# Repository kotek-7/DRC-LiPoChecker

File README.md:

リポチェッカーです  
KiCad ↓  
https://kicanvas.org/?repo=https%3A%2F%2Fgithub.com%2Fkotek-7%2FDRC-LiPochecker

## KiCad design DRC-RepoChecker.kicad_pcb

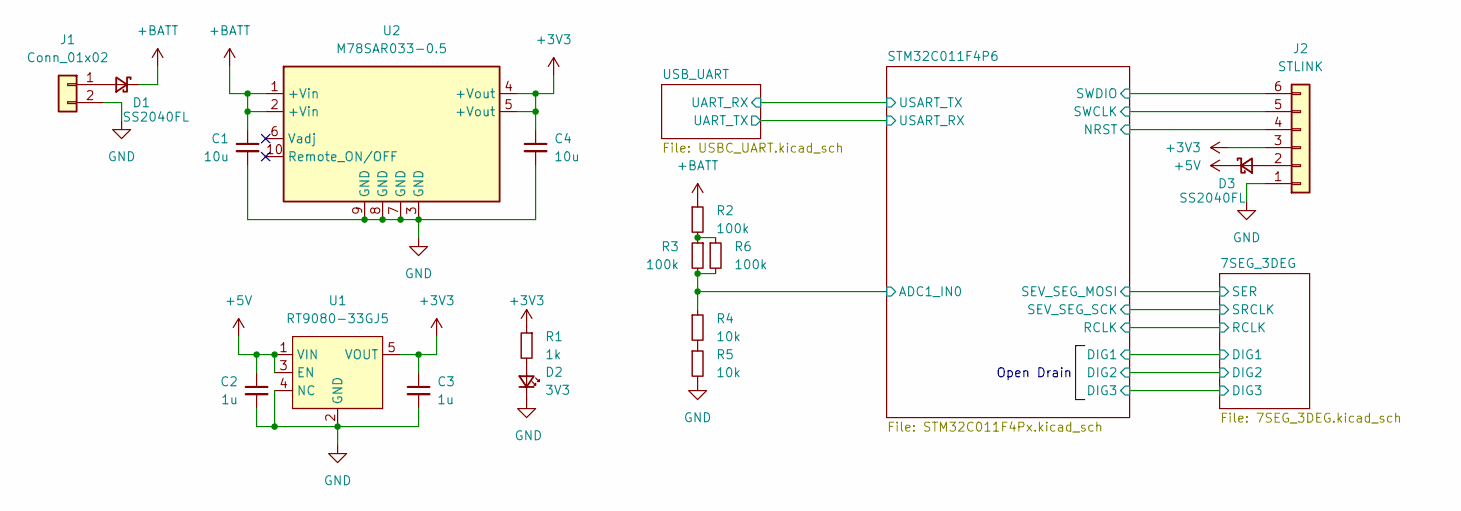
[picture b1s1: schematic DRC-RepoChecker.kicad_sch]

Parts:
C1, C4: 10u; C_0805_2012Metric_Pad1.18x1.45mm_HandSolder
C2, C3: 1u; C_0603_1608Metric_Pad1.08x0.95mm_HandSolder
D1, D3: SS2040FL; D_SOD-123F
D2: 3V3; LED_0603_1608Metric_Pad1.05x0.95mm_HandSolder
J1: Conn_01x02; AMASS_XT30PW-M_1x02_P2.50mm_Horizontal
J2: STLINK; IDC-Header_2x03_P2.54mm_Vertical
R1: 1k; R_0603_1608Metric_Pad0.98x0.95mm_HandSolder
R2, R3, R6: 100k; R_0603_1608Metric_Pad0.98x0.95mm_HandSolder
R4, R5: 10k; R_0603_1608Metric_Pad0.98x0.95mm_HandSolder
U1: RT9080-33GJ5; TSOT-23-5
U2: M78SAR033-0.5

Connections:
+3V3: C3.1, C4.1, J2.3, R1.1, U1.5 (VOUT), U2.4 (+Vout), U2.5 (+Vout); also elsewhere on the board
+5V: C2.1, D3.1 (K), U1.1 (VIN), U1.3 (EN); also elsewhere on the board
+BATT: C1.1, D1.1 (K), R2.1, U2.1 (+Vin), U2.2 (+Vin)
/STM32C011F4P6/ADC1_IN0: R3.2, R4.1, R6.2; also elsewhere on the board
/STM32C011F4P6/NRST: J2.4; also elsewhere on the board
/STM32C011F4P6/SWCLK: J2.5; also elsewhere on the board
/STM32C011F4P6/SWDIO: J2.6; also elsewhere on the board
GND: C1.2, C2.2, C3.2, C4.2, D2.1 (K), J1.2, J2.1, R5.2, U1.2 (GND), U1.4 (NC), U2.3 (GND), U2.7 (GND), U2.8 (GND), U2.9 (GND); also elsewhere on the board
unnamed: D1.2 (A), J1.1
unnamed: D2.2 (A), R1.2
unnamed: D3.2 (A), J2.2
unnamed: R2.2, R3.1, R6.1
unnamed: R4.2, R5.1

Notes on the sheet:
Open Drain

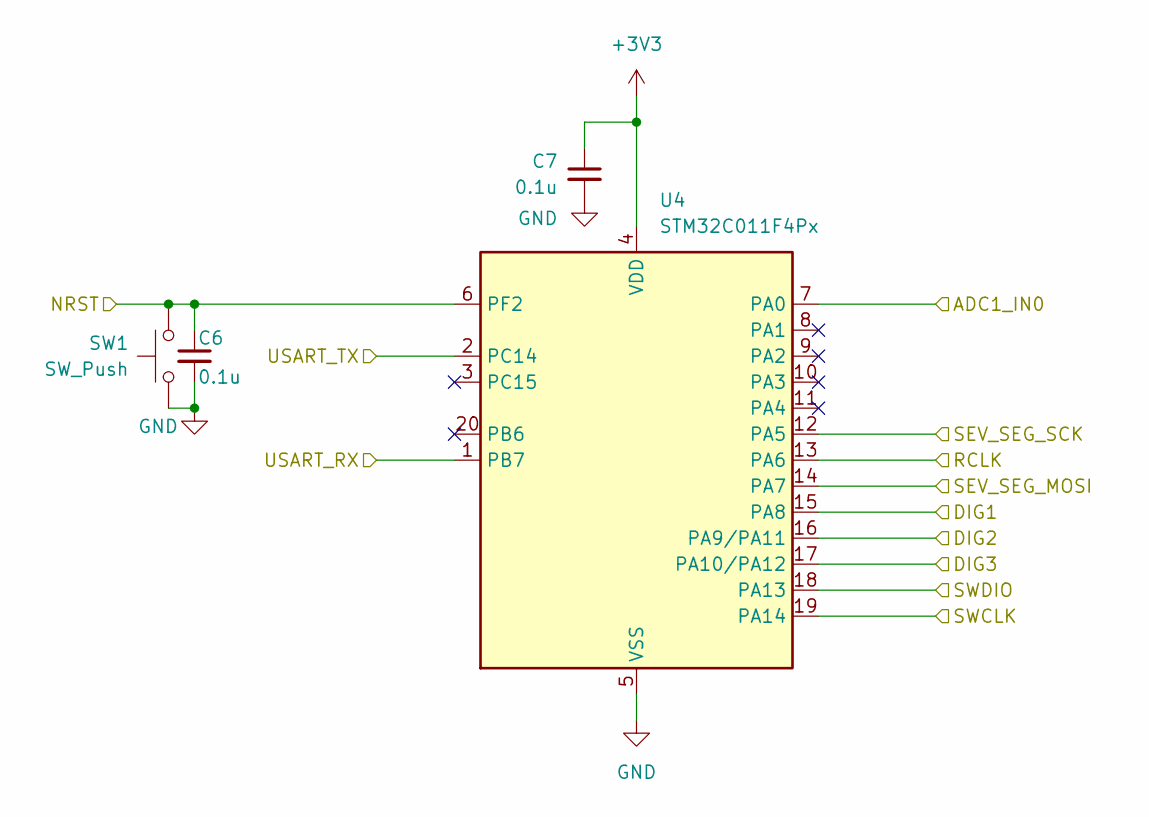
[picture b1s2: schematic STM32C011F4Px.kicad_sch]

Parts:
C6, C7: 0.1u; C_0603_1608Metric_Pad1.08x0.95mm_HandSolder
SW1: SW_Push; TVAF06-A020B-R
U4: STM32C011F4Px; TSSOP-20_4.4x6.5mm_P0.65mm

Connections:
+3V3: C7.1, U4.4 (VDD); also elsewhere on the board
/7SEG_3DEG/DIG1: U4.15 (PA8); also elsewhere on the board
/7SEG_3DEG/DIG2: U4.16 (PA9/PA11); also elsewhere on the board
/7SEG_3DEG/DIG3: U4.17 (PA10/PA12); also elsewhere on the board
/7SEG_3DEG/RCLK: U4.13 (PA6); also elsewhere on the board
/7SEG_3DEG/SER: U4.14 (PA7); also elsewhere on the board
/7SEG_3DEG/SRCLK: U4.12 (PA5); also elsewhere on the board
/STM32C011F4P6/ADC1_IN0: U4.7 (PA0); also elsewhere on the board
/STM32C011F4P6/NRST: C6.1, SW1.1, U4.6 (PF2); also elsewhere on the board
/STM32C011F4P6/SWCLK: U4.19 (PA14); also elsewhere on the board
/STM32C011F4P6/SWDIO: U4.18 (PA13); also elsewhere on the board
/STM32C011F4P6/USART_RX: U4.1 (PB7); also elsewhere on the board
/STM32C011F4P6/USART_TX: U4.2 (PC14); also elsewhere on the board
GND: C6.2, C7.2, SW1.2, U4.5 (VSS); also elsewhere on the board

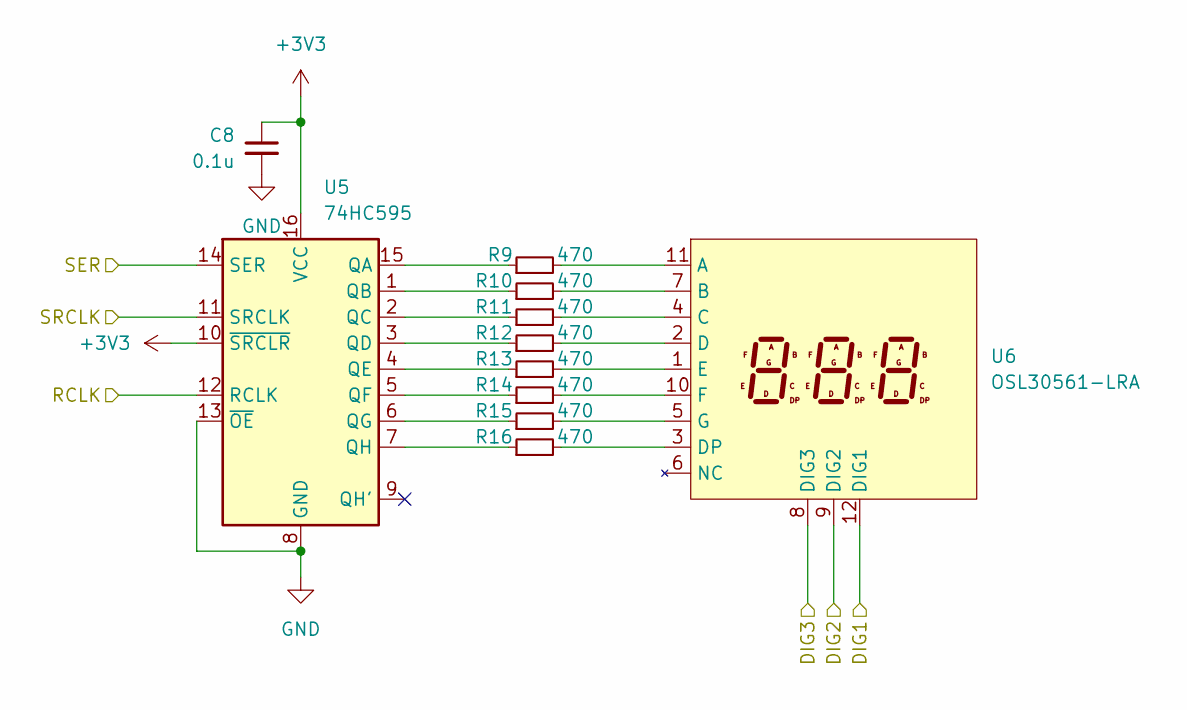
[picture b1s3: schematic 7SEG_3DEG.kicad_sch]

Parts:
C8: 0.1u; C_0603_1608Metric_Pad1.08x0.95mm_HandSolder
R9, R10, R11, R12, R13, R14, R15, R16: 470; R_0603_1608Metric_Pad0.98x0.95mm_HandSolder
U5: 74HC595; SOP-16_4.55x10.3mm_P1.27mm
U6: OSL30561-LRA

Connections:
+3V3: C8.1, U5.10 (~SRCLR), U5.16 (VCC); also elsewhere on the board
/7SEG_3DEG/DIG1: U6.12 (DIG1); also elsewhere on the board
/7SEG_3DEG/DIG2: U6.9 (DIG2); also elsewhere on the board
/7SEG_3DEG/DIG3: U6.8 (DIG3); also elsewhere on the board
/7SEG_3DEG/RCLK: U5.12 (RCLK); also elsewhere on the board
/7SEG_3DEG/SER: U5.14 (SER); also elsewhere on the board
/7SEG_3DEG/SRCLK: U5.11 (SRCLK); also elsewhere on the board
GND: C8.2, U5.8 (GND), U5.13 (~OE); also elsewhere on the board
unnamed: R9.1, U5.15 (QA)
unnamed: R10.1, U5.1 (QB)
unnamed: R11.1, U5.2 (QC)
unnamed: R12.1, U5.3 (QD)
unnamed: R13.1, U5.4 (QE)
unnamed: R14.1, U5.5 (QF)
unnamed: R15.1, U5.6 (QG)
unnamed: R16.1, U5.7 (QH)
unnamed: R9.2, U6.11 (A)
unnamed: R10.2, U6.7 (B)
unnamed: R11.2, U6.4 (C)
unnamed: R12.2, U6.2 (D)
unnamed: R16.2, U6.3 (DP)
unnamed: R13.2, U6.1 (E)
unnamed: R14.2, U6.10 (F)
unnamed: R15.2, U6.5 (G)

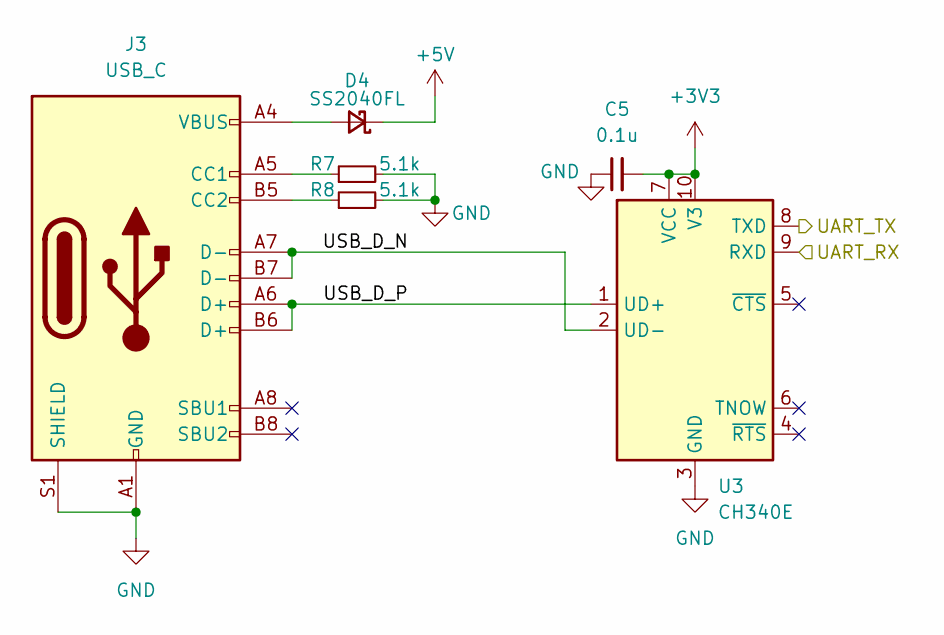
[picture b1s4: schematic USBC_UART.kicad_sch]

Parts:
C5: 0.1u; C_0603_1608Metric_Pad1.08x0.95mm_HandSolder
D4: SS2040FL; D_SOD-123F
J3: USB_C; USB_C_Receptacle_GCT_USB4105-xx-A_16P_TopMnt_Horizontal
R7, R8: 5.1k; R_0603_1608Metric_Pad0.98x0.95mm_HandSolder
U3: CH340E; MSOP-10_3x3mm_P0.5mm

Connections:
+3V3: C5.2, U3.7 (VCC), U3.10 (V3); also elsewhere on the board
+5V: D4.1 (K); also elsewhere on the board
/STM32C011F4P6/USART_RX: U3.8 (TXD); also elsewhere on the board
/STM32C011F4P6/USART_TX: U3.9 (RXD); also elsewhere on the board
/USB_UART/USB_D_N: J3.A7 (D-), J3.B7 (D-), U3.2 (UD-)
/USB_UART/USB_D_P: J3.A6 (D+), J3.B6 (D+), U3.1 (UD+)
GND: C5.1, J3.A1 (GND), J3.A12 (GND), J3.B1 (GND), J3.B12 (GND), J3.S1 (SHIELD), R7.2, R8.2, U3.3 (GND); also elsewhere on the board
unnamed: D4.2 (A), J3.A4 (VBUS), J3.A9 (VBUS), J3.B4 (VBUS), J3.B9 (VBUS)
unnamed: J3.A5 (CC1), R7.1
unnamed: J3.B5 (CC2), R8.1

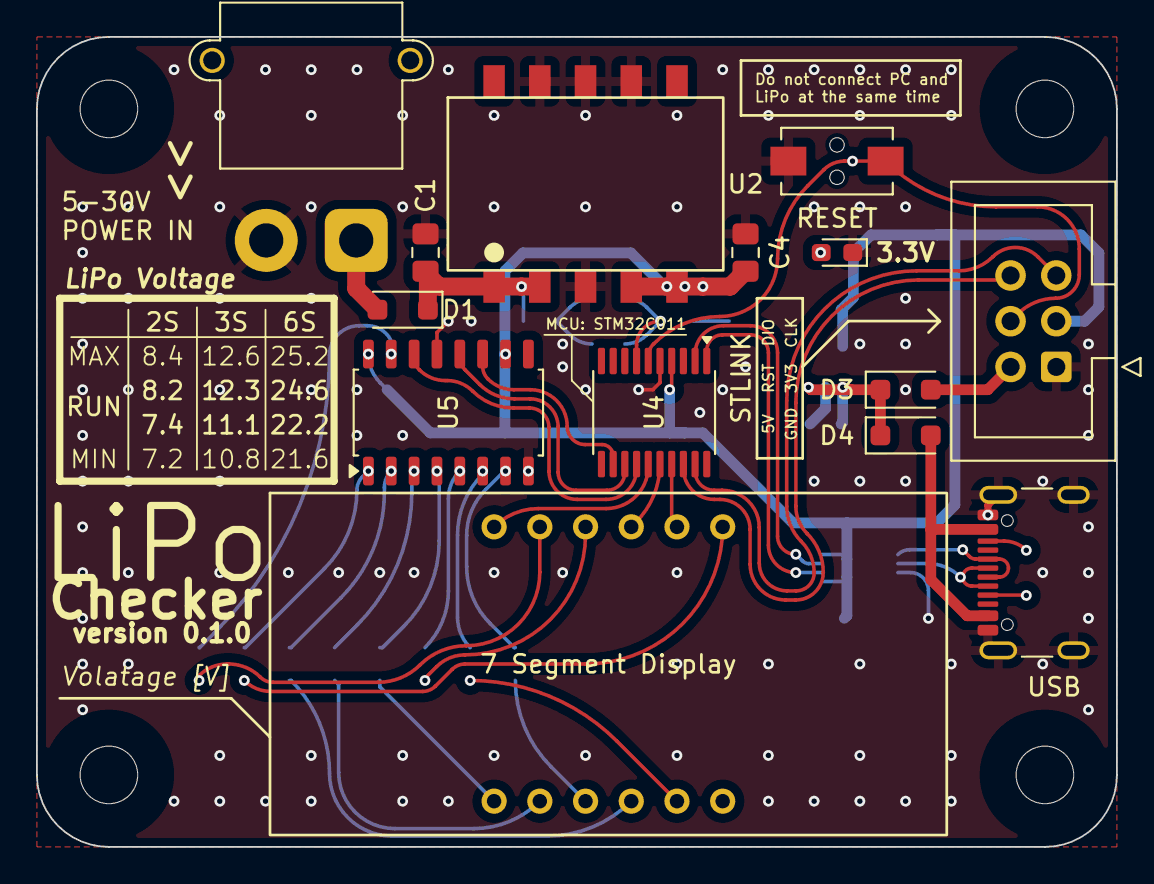
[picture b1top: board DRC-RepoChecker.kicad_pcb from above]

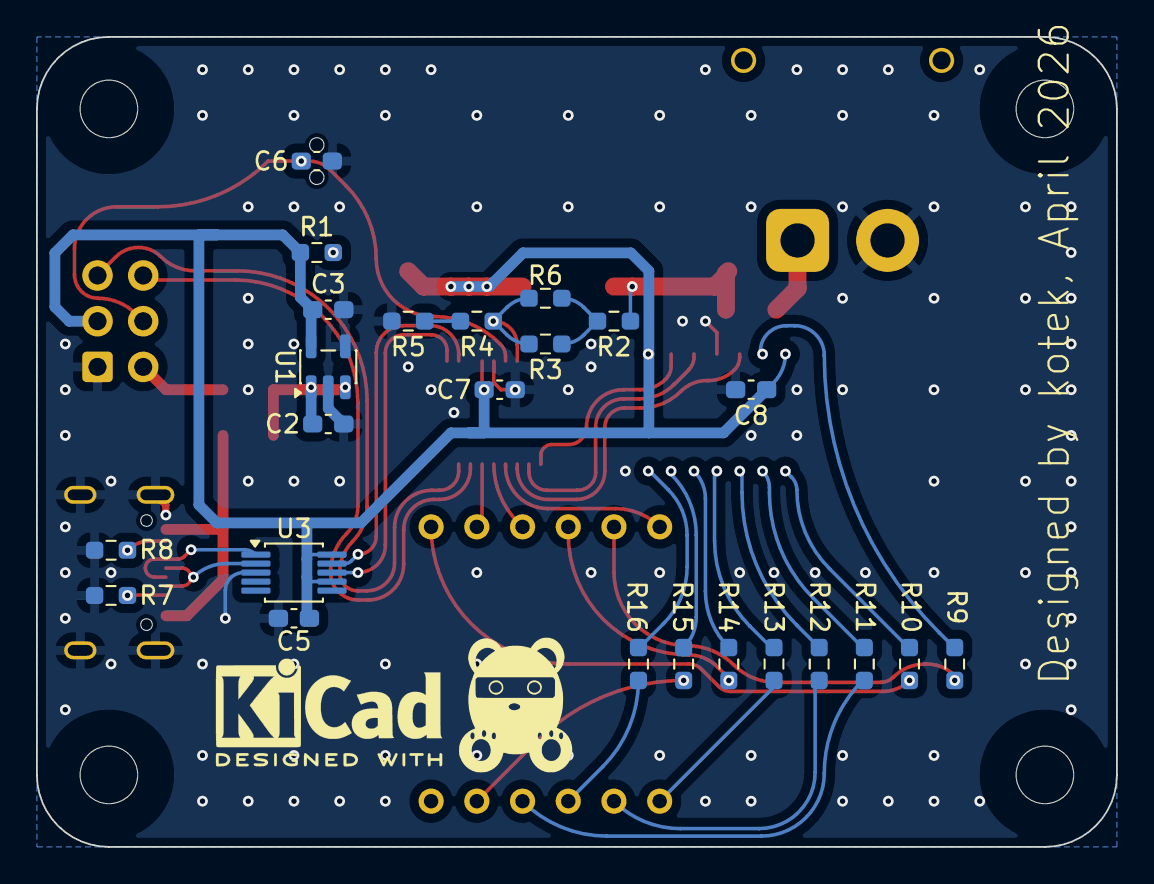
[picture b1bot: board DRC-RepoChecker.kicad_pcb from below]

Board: 2 copper layers, 60.0 x 45.0 mm, 38 parts (24 on the bottom side), 42 nets.

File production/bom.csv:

Designator,Footprint,Quantity,Value,LCSC Part #
"C1, C4",0805,2,10u,
"C2, C3",0603,2,1u,
"C5, C6, C7, C8",0603,4,0.1u,
"D1, D3, D4",D_SOD-123F,3,SS2040FL,
D2,0603,1,3V3,
J1,AMASS_XT30PW-M_1x02_P2.50mm_Horizontal,1,Conn_01x02,
J2,IDC-Header_2x03_P2.54mm_Vertical,1,STLINK,
J3,USB_C_Receptacle_GCT_USB4105-xx-A_16P_TopMnt_Horizontal,1,USB_C,
R1,0603,1,1k,
"R10, R11, R12, R13, R14, R15, R16, R9",0603,8,470,
"R2, R3, R6",0603,3,100k,
"R4, R5",0603,2,10k,
"R7, R8",0603,2,5.1k,
SW1,TVAF06-A020B-R,1,SW_Push,
U1,TSOT-23-5,1,RT9080-33GJ5,
U2,M78SAR033-0.5,1,M78SAR033-0.5,
U3,MSOP-10_3x3mm_P0.5mm,1,CH340E,
U4,TSSOP-20_4.4x6.5mm_P0.65mm,1,STM32C011F4Px,
U5,SOP-16_4.55x10.3mm_P1.27mm,1,74HC595,
U6,OSL30561-LRA,1,OSL30561-LRA,

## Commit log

2026-04-19 initial commit, v0.1.0
2026-04-19 READMEを変更
2026-04-19 シルクのミスを修正
2026-04-19 謎の修正
2026-04-19 不要なファイルを追跡から削除
2026-04-19 シルクを修正
